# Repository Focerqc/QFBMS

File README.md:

# QFBMS — 32s charge-only BMS

QFBMS is a 32-series, charge-only battery-management board for a Fungineers pack. It uses two BQ76952 monitors and an ESP32-C3-MINI-1. The intended software is the VBMS32-target VESC Express firmware plus the supplied VBMS32 Micro package.

The board monitors cells and temperature, measures charging current, controls charging, and balances cells. **Discharge protection is outside the build scope.**

The circuit and routing are incomplete. Firmware compatibility is a design target; the current PCB has not been verified against the supplied software or validated for manufacture.

## Start here

- [Build plan](PLAN.md): the current objective, work order, open decisions, and completion criteria.
- [Design rules](DESIGN_RULES.md): mechanical constraints and how to change the working design.
- [Firmware and package interface](docs/FIRMWARE_INTERFACE.md): behavior and hardware assumptions already defined by the supplied software.

These documents supersede the proposals in [docs/history](docs/history/README.md). The historical discharge-switching instructions and blanket prohibition on moving any component are not the current build plan.

## What stays in place

Keep the placed connectors and bleed resistors R_B1–R_B33 in their existing locations for compatibility with the same case. There is no heatsink. Keep the two BMS monitors in approximately their existing areas; modest local adjustment is acceptable when needed for a sound layout.

Supporting circuitry should follow TI's applicable electrical and layout guidance while fitting these constraints. The existing C_F1–C_F32 back-side placement is a separate unresolved issue; see [Design rules](DESIGN_RULES.md).

## How the software controls the board

The package's LispBM program runs on the ESP32 inside VESC Express. It decides when charging and balancing are allowed. The board-specific C firmware supplies the hardware functions: reading the BQ monitors and commanding balancing over I2C, and controlling external charge-switch circuitry through ESP32 GPIOs.

The supplied package already implements charging voltage, temperature, and current limits, plus balancing rules. Use those definitions as the compatibility baseline. Review the physical circuit, sensing calibration, and startup wiring against them before routing. The BQ automatic-protection configuration alone does not describe the complete charging behavior.

TI supplies the electrical requirements for the monitors and their supporting circuits. A 32s design also needs the stacked-monitor communication and power-domain treatment described in [the reference notes](_reference/ti_bq76952/README.md).

## Open the design

Open `qfbms32.kicad_pro` in KiCad 10. Keep the PCB, schematic, custom footprints in `qfbms.pretty/`, footprint table, and local `3dmodels/` together.

The PCB pad nets are the current working copy. The schematic is incomplete and must be reconciled deliberately; do not overwrite the PCB with an unverified schematic netlist or an old generation script.

The saved [connectivity snapshot](docs/connectivity-snapshot.json) is a migration-era report, not a live status or electrical sign-off. Read the actual board for current connectivity. Dashboard criteria may still reflect older topology assumptions.

## Local tools

From this repository root, install the dashboard dependencies:

```powershell
python -m pip install -r requirements.txt
```

Run each dashboard in its own terminal:

```powershell
python _tools/progress_dashboard/server.py
# http://localhost:5181
```

```powershell
python _tools/pcb_dashboard/server.py
# http://localhost:5180
```

Stop older copies using those ports first. The tools currently expect KiCad 10 at `C:\Program Files\KiCad\10.0`; scripts importing `pcbnew` use KiCad's bundled Python.

## References and history

- [_reference/firmware/](_reference/firmware/): supplied VBMS32 firmware and package source, retained as the compatibility baseline.
- [_reference/ti_bq76952/](_reference/ti_bq76952/README.md): datasheet, evaluation-board material, and links to stacked-monitor guidance.
- [_reference/user_photos/](_reference/user_photos/): placement photographs; IMG_2151 shows the back.
- [Harness drawing](_reference/vfbms32_wiring_32s_best.jpg): external wiring reference; verify its connector pin mapping against the PCB.
- [_reference/pinouts/](_reference/pinouts/): preserved component pinout research.
- [docs/history/](docs/history/README.md): superseded topology, inventory, and finish instructions, retained for traceability.
- [exports/](exports/README.md): regenerated previews and reports, ignored by Git.

The original folder, experiments, and backups remain in the local source repository's migration archive. See [Migration history](docs/MIGRATION.md).

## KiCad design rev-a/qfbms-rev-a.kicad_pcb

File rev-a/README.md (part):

# QFBMS rev A

A fresh, generated attempt at the 32s charge-only BMS. It keeps the old board's outline,
connectors and R_B1–R_B33 row, and the supplied VBMS32 firmware. Everything else was redrawn
from the datasheets.

**Status (2026-11-17):** complete schematic, every part has a stated purpose, placed and
routed on 4 layers with shaped charge-path pours. **Not ready to order:** 4 connections are still
open and 7 small DRC items remain (list below), and the design assumes a conformal-coated board.
Work stopped here on purpose: rev A is a reference model, not a build commitment. Rev A is a guess-and-check
build. An outside review (below) found one critical circuit error and several major ones, so
**as drawn it would not work safely**. They are recorded, not fixed: the PCB is left as is.

| Check | Result |
|---|---|
| Parts | 193, each with a `Purpose` field (schematic property, footprint field and [bom.csv](bom.csv)) |
| Netlist vs. circuit table | 562 pins checked by kicad-cli, 0 mismatches, 0 single-pin nets |
| ERC | 0 errors, 1 expected warning (isolator GND2 sits on CELL16) |
| Fixed parts | 45 checked (connectors + R_B1–R_B33): position, rotation, side, every pad identical to `qfbms32.kicad_pcb` |
| Placement | 193/193 on the front, each inside its voltage domain (upper monitor between x 41 and 63) |
| Routing | Freerouting, 4 layers, In1 = GND / CELL16 reference planes |
| PCB DRC (coated rules) | Schematic parity 0, **4 unconnected**, 7 small errors (2 GND tracks too near the edge, 4 starved thermal reliefs, 1 dangling stub). Also 3 pin-to-pin pairs set by TI's pinouts and 6 items in the fixed parts' own footprints (see `route/drc-summary.json`) |
| PCB DRC (uncoated, 0.6 mm by voltage bank) | ~280 clearance hits: not met. Use conformal coating or re-route by hand |

## Files

| Path | What |
|---|---|
| `tools/circuit.py` | **The design.** Every part, pin→net map, value, MPN and purpose |
| `tools/gen_schematic.py` | Writes `qfbms-rev-a.kicad_sch`, `bom.csv`, the local symbol lib and lib tables |
| `tools/check_schematic.py` | kicad-cli netlist parity against `circuit.py`, plus ERC |
| `tools/build_board.py` | Writes `qfbms-rev-a.kicad_pcb` from the old board's outline and fixed parts (old file only read) and places every part by connectivity inside its voltage domain |
| `tools/set_rules.py` | Net classes (Default / POWER / HV / CHARGE) and `.kicad_dru`. `--uncoated` writes the 0.6 mm voltage-bank rules |
| `tools/route_board.py` | `export` adds the In1 planes and writes `route/*.dsn`; `import` reads Freerouting's `.ses` |
| `tools/check_board.py` | DRC + parity, sorted into real problems, chip-pinout pairs and fixed-footprint items |
| `qfbms_reva.pretty/`, `qfbms_reva.kicad_sym` | XT30, USB-C, ESP32, buzzer footprints (copied); ESP32-C3-MINI-1 and VOM1271 symbols |
| `render/` | Board render and schematic PDF |

Regenerate (KiCad 10; `KPY` = `"C:\Program Files\KiCad\10.0\bin\python.exe"`):

```
python tools/gen_schematic.py && python tools/check_schematic.py
python tools/set_rules.py
KPY tools/build_board.py
KPY tools/route_board.py export
java -jar freerouting-2.0.1.jar -de route/qfbms-rev-a.dsn -do route/qfbms-rev-a.ses -mp 100 -mt 1 -da
KPY tools/route_board.py import --no-pours
python tools/check_board.py
```

Freerouting 2.0.1 needs Java 21. Headless mode (`--gui.enabled=false`) exits without saving.
With the window it routes, saves, shows a settings pop-up and closes itself. Its settings file
(`%TEMP%\freerouting\freerouting.json`) enables telemetry by default; it was switched off here.
`route/placed-planes.kicad_pcb` is the placed, unrouted board the current route came from.

Change the design in `circuit.py` only. The schematic is label-per-pin and is never edited by hand.

## How it works

- **Monitors.** Two BQ7695202 (I2C with CRC, REG1 on at 3.3 V: what the firmware expects).
  U_BQ1 does cells 1–16 against GND. U_BQ2 does cells 17–32 against CELL16. Each has TI's
  typical supply: a BAT diode with RC, a BCX56-16 (80 V, SOT-89) REG0 preregulator with its own collector
  diode, a 10 MΩ BREG resistor, 22 nF on REGIN, 2.2 µF on REG18, 1 µF on REG1, and 2.2 µF from CP1 to BAT.
- **Cell inputs.** R_B1–R_B33 (27 Ω, fixed row) are the cell input resistors, one per tap.
  Tap 16 is shared by both monitors. 32 × 100 nF differential capacitors. Internal balancing ≈ 50 mA.
- **Always awake.** A 10 kΩ from TS2 to VSS wakes each monitor from SHUTDOWN (TI's note on
  thermistors at TS2). The firmware only uses DEEPSLEEP, so no wake circuit is needed.
  PACK has 10 kΩ to its own top of stack and LD goes to VSS (TI: no high-side FETs).
- **Current.** One 1 mΩ shunt between BAT− and charger negative, Kelvin-tied with net ties,
  100 Ω/100 nF filter. The Micro package scales the firmware's 0.2 mΩ gain by −0.2, so 1 mΩ
  with SRP on the battery side is what it expects (PCB_VERSION 2). No firmware change needed.
- **Temperatures.** J_T1–J_T4 go to TS1, TS3, ALERT and DCHG. RT1, beside the FETs, goes to HDQ.
  Each has a 499 Ω series resistor (the firmware subtracts 500 Ω), with a 10 k B3380 NTC.
- **Charge switch.** Q1 and Q2 are back-to-back 200 V N-FETs (TOLL), so the charge port is dead
  either way when off. A VOM1271 photovoltaic driver makes the floating ~8 V gate drive with
  no high-side supply. Its LED needs both CHG_EN (GPIO5) **and** PSW_EN (GPIO10), matching the
  firmware's order.
- **Upper-monitor link.** The host I2C bus goes through two 74CBTLV1G125 bus switches to an
  ISO1640. COM_EN (GPIO9) high opens the switches, so the firmware can re-address U_BQ1
  while U_BQ2 is hidden. The isolator's upper side runs from U_BQ2's REG1 through a PFET.
  An opto turns that PFET on only while COM_EN is low, so the isolator doesn't drain cells
  17–32 in sleep.
- **Power.** LTC7138 (140 V) from the fused pack through a 100 Ω/2 µF filter, to 5.0 V. It is
  diode-ORed with USB VBUS, then an AP2112K makes 3.3 V. The ESP32 can be flashed over USB
  without the pack.
- **ESP32-C3-MINI-1.** Pins exactly as `hw_vbms32.h`. GPIO2 (ENABLE) idles low with a wake
  button to 3.3 V, because the firmware treats high as "stay awake". GPIO8/GPIO9 straps are
  pulled high. 2.2 MΩ/47 kΩ dividers keep the firmware's 220k/4.7k ratio at 1/10 the drain.
- **CAN.** ISO1050 isolated, side 2 powered from the VESC's 5 V on J_COMM1, with an optional
  120 Ω termination behind solder jumper JP1.

## Removed from the old board, and why

| Old parts | Why they are gone |
|---|---|
| R_F1–R_F32 (20 Ω) | Second series row. R_B1–R_B33 already are the cell input resistors |
| R_SH2 | Second shunt. One 1 mΩ matches the firmware scaling |
| U_SSR1 "GSRELAY", C_SSR1/2, R_SSR1/2 | Unidentified relay/driver. Replaced by the VOM1271 |
| D_BST1, D_PRI1–3, D_SEC1–3, R_SEC1, FB1, C_TAN1, C_FLT1, C_DISC | Old boost/isolated-supply gate-drive attempt. The photovoltaic driver needs none of it |
| D_CHG1–3 (DSK320), R_CHG1/2, R_DSG1, R_S1/2, R_G1, R_GS1, D_GS1, D_S1 | Old charge/discharge-path parts. Discharge is out of scope; the new charge path is Q1/Q2, R1, D1 |
| EP pad on U_BQ1/U_BQ2 footprints | The BQ76952 TQFP-48 has no exposed pad |

U4 (LTC7138), U7 (ISO1050), Q1, F1, BZ1, the C_F caps and U_BQ1/U_BQ2 keep their references
with new circuits.

## External review (2026-11-17, recorded, not fixed)

A ChatGPT review of `circuit.py`, the README, the BOM, the firmware and the PCB. Its local
copies were used; it could not open the public links. The top finding was checked against
`circuit.py` and is correct. Decision: leave the PCB as is and record everything here.

### Hardware (rev A design errors)

| Severity | Part / net | Finding | Fix if rev B happens |
|---|---|---|---|
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
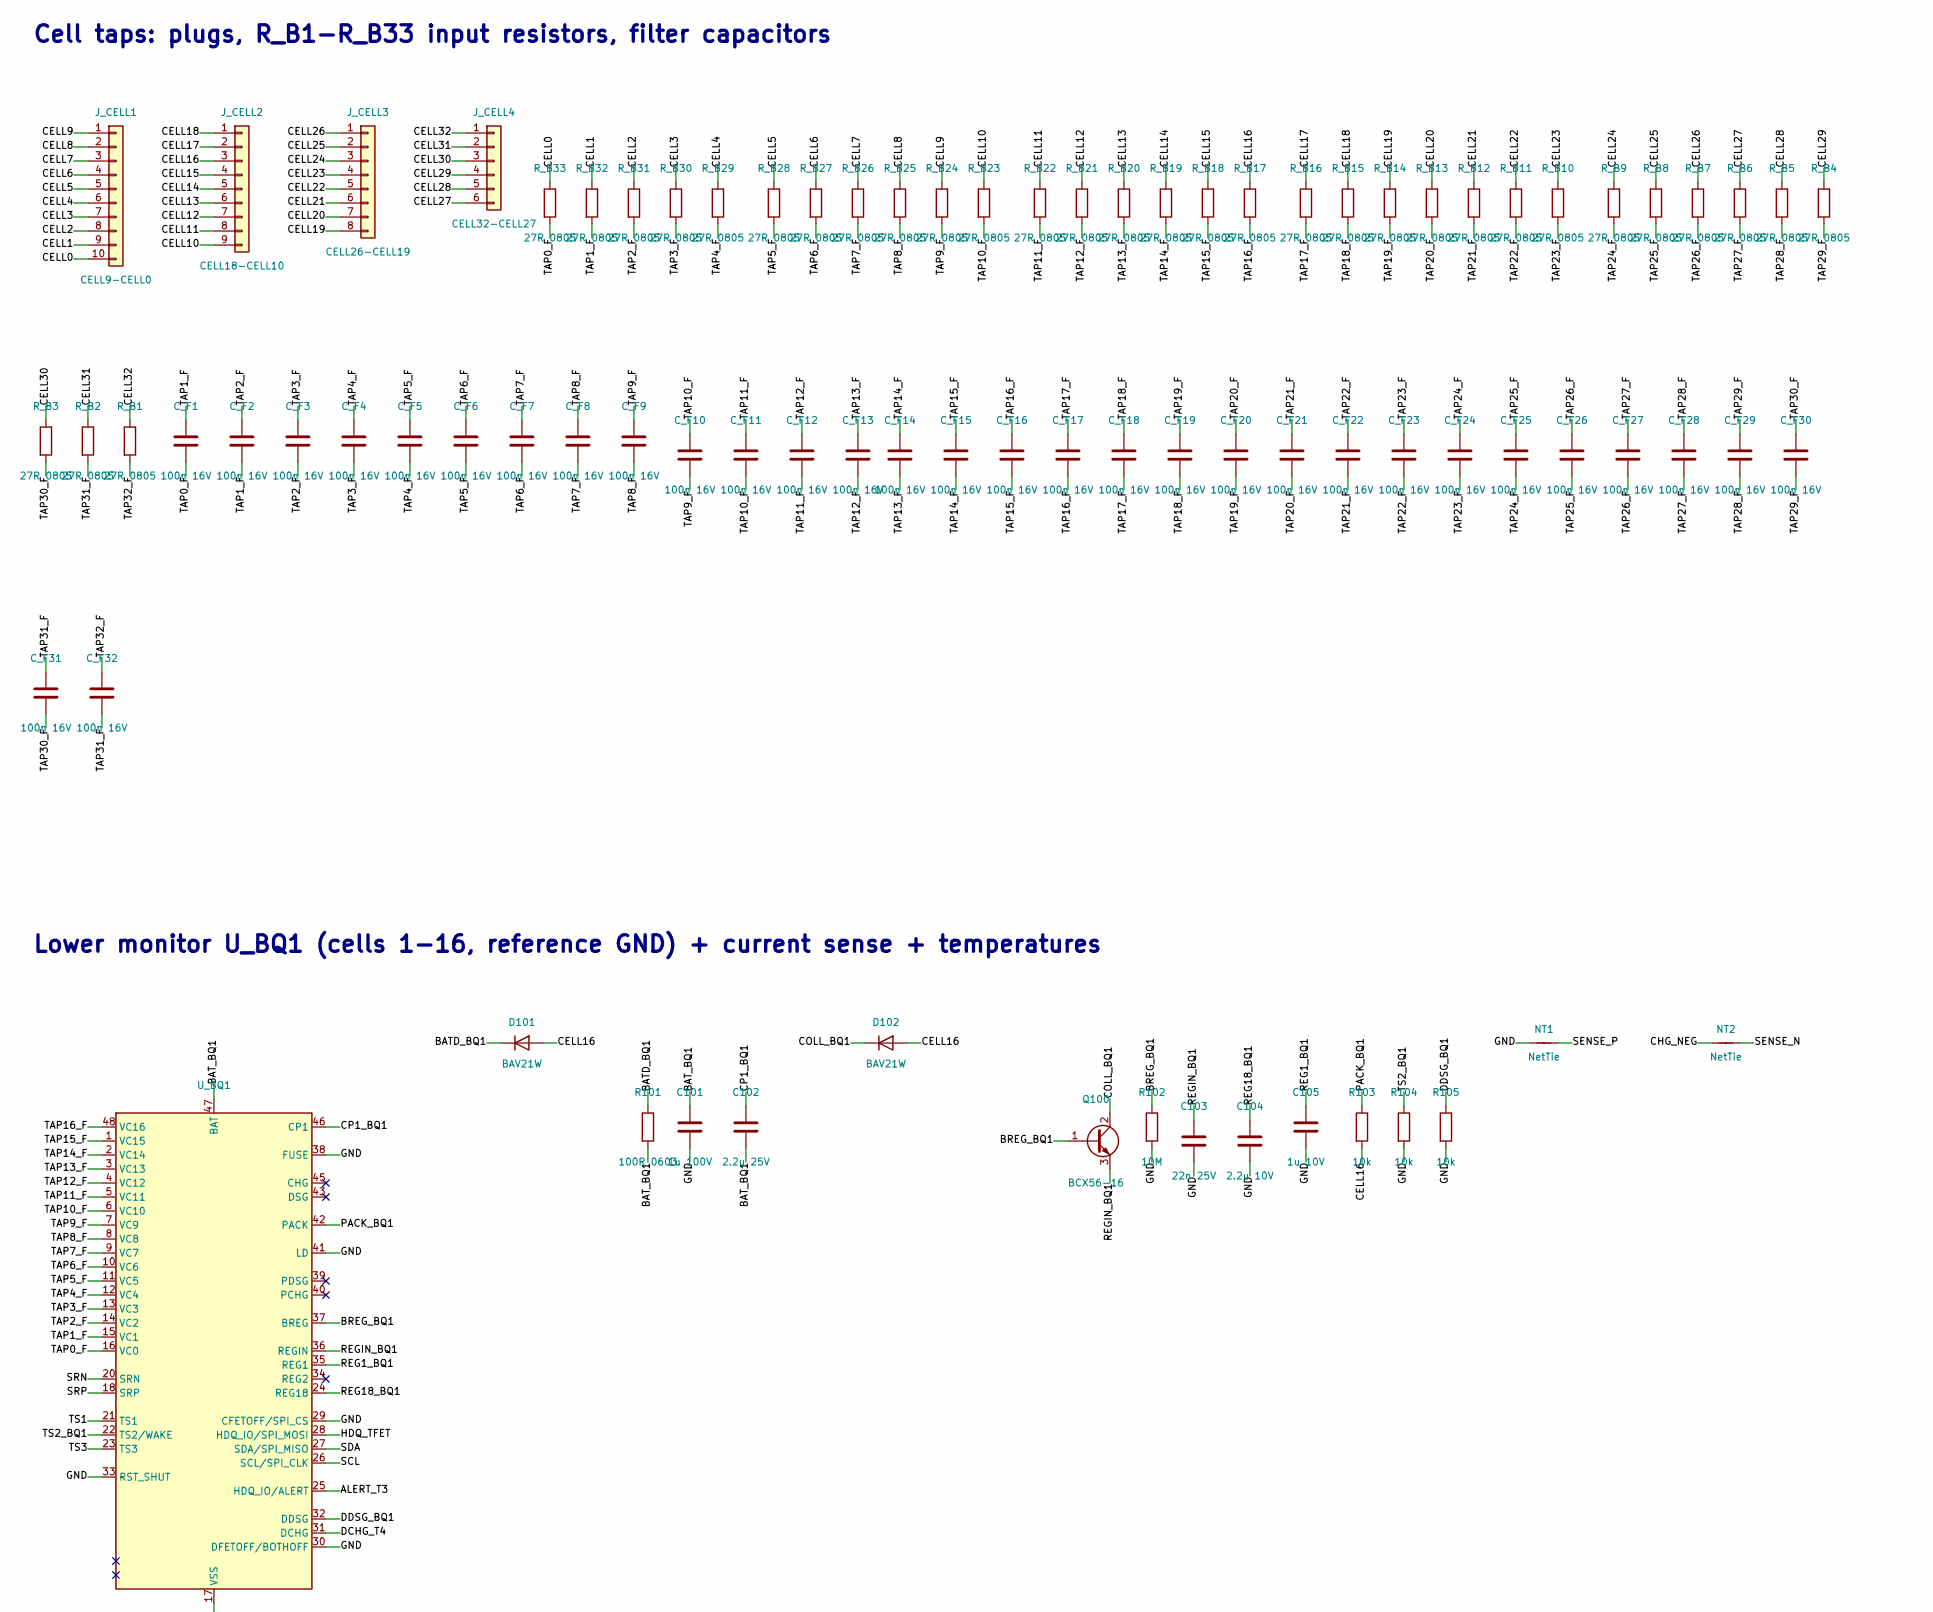
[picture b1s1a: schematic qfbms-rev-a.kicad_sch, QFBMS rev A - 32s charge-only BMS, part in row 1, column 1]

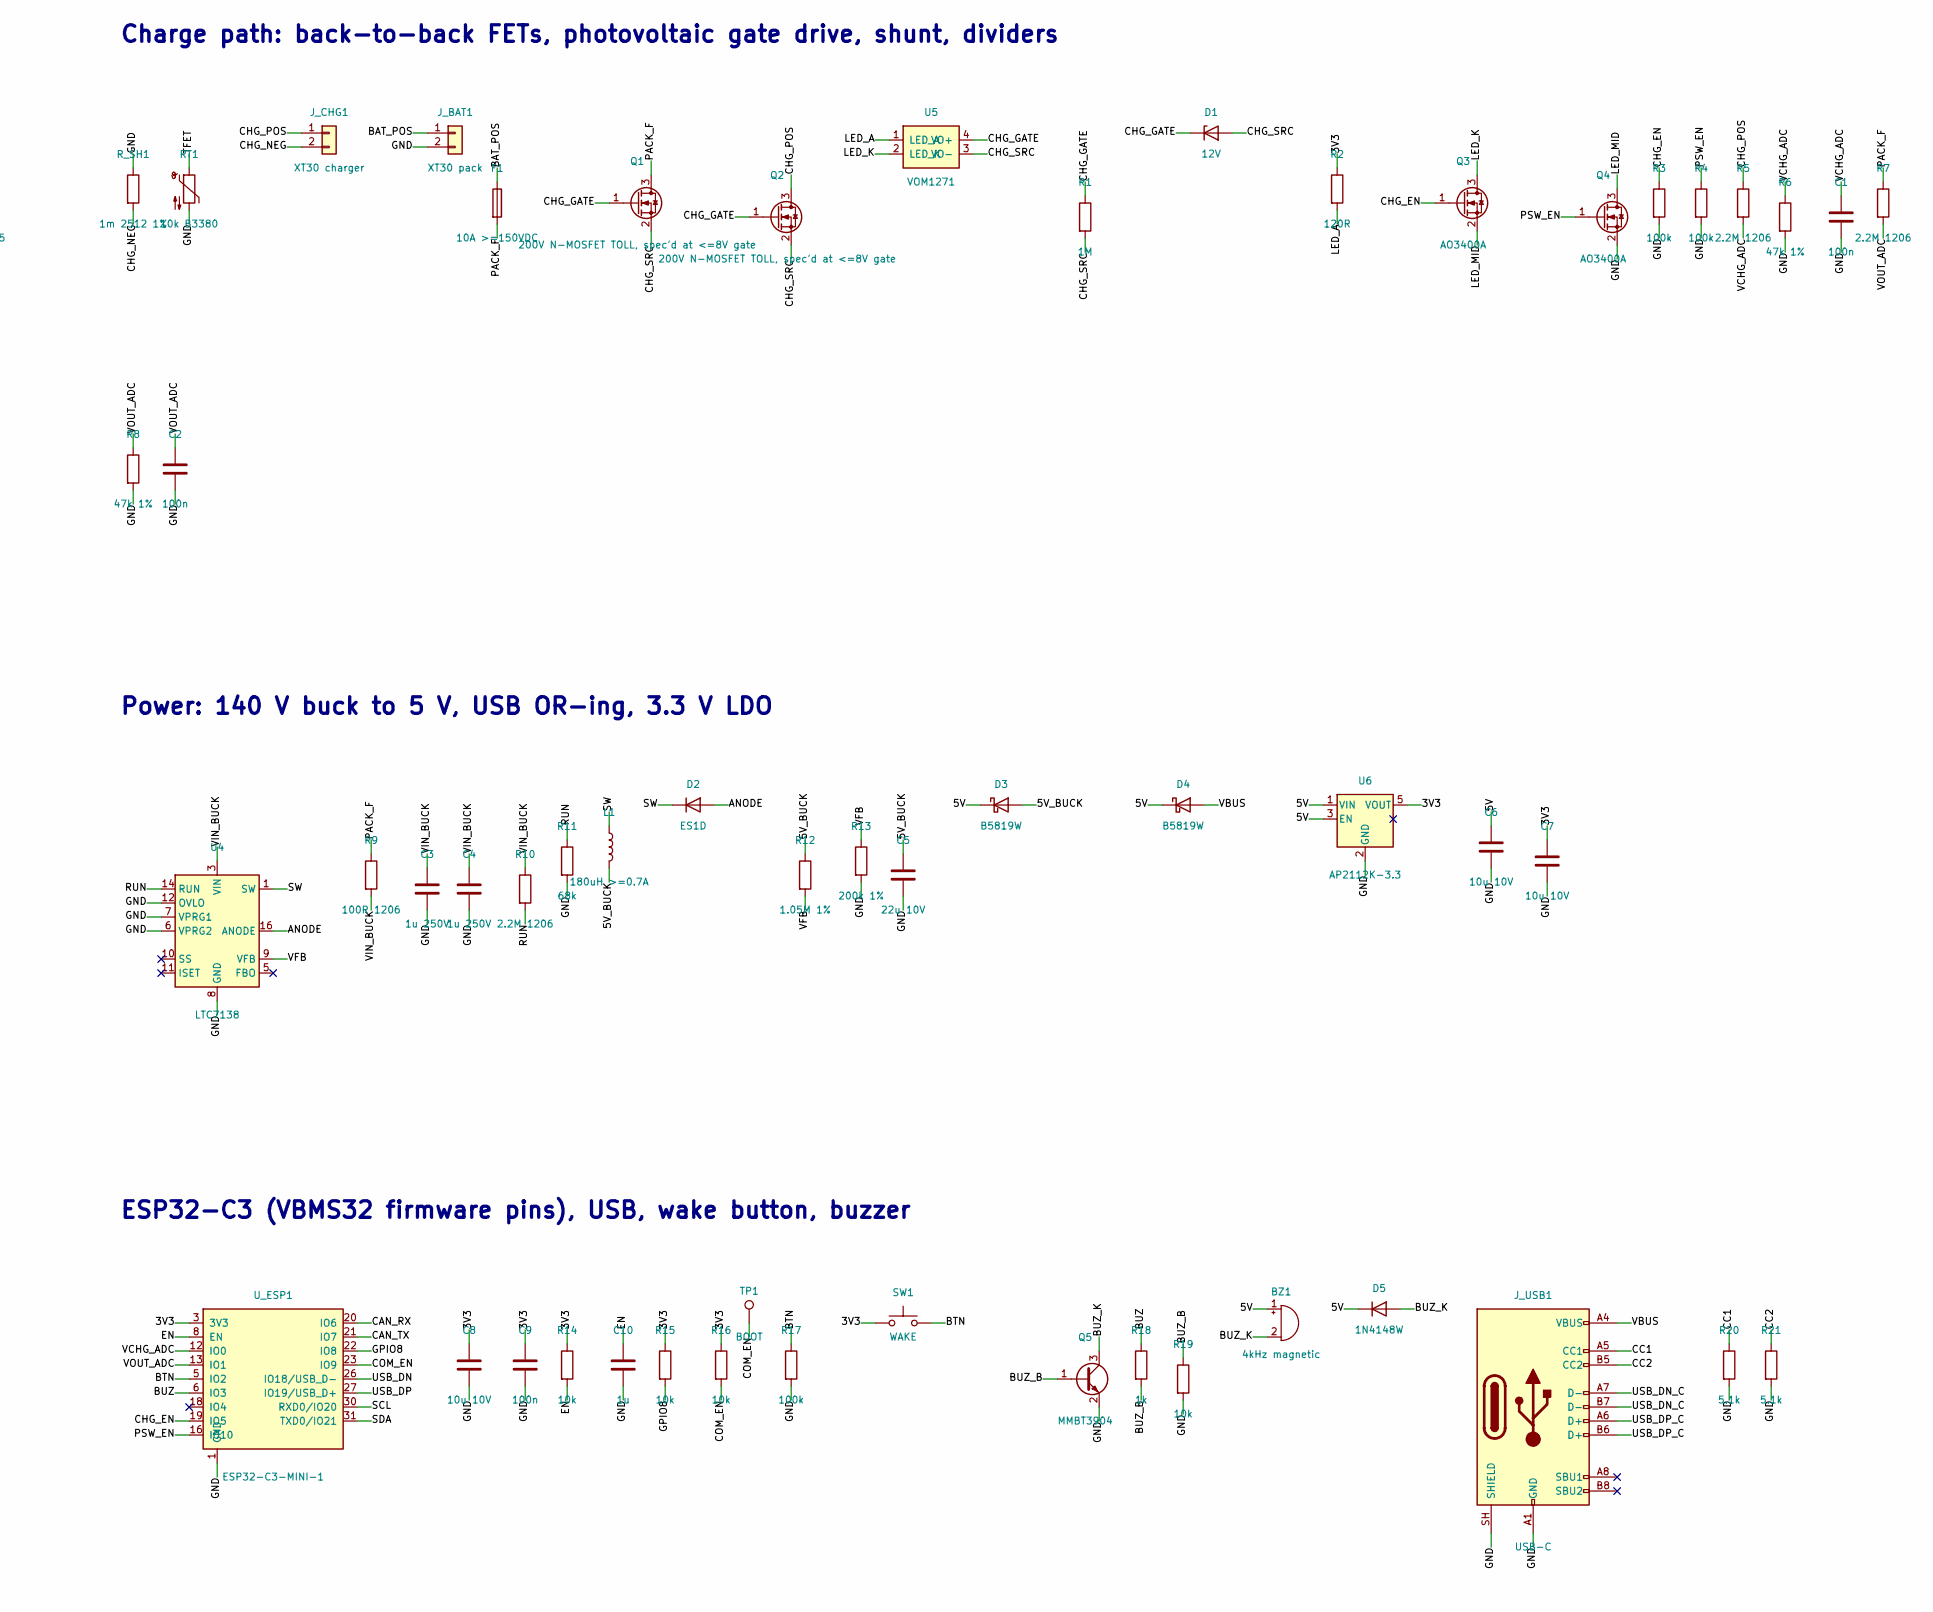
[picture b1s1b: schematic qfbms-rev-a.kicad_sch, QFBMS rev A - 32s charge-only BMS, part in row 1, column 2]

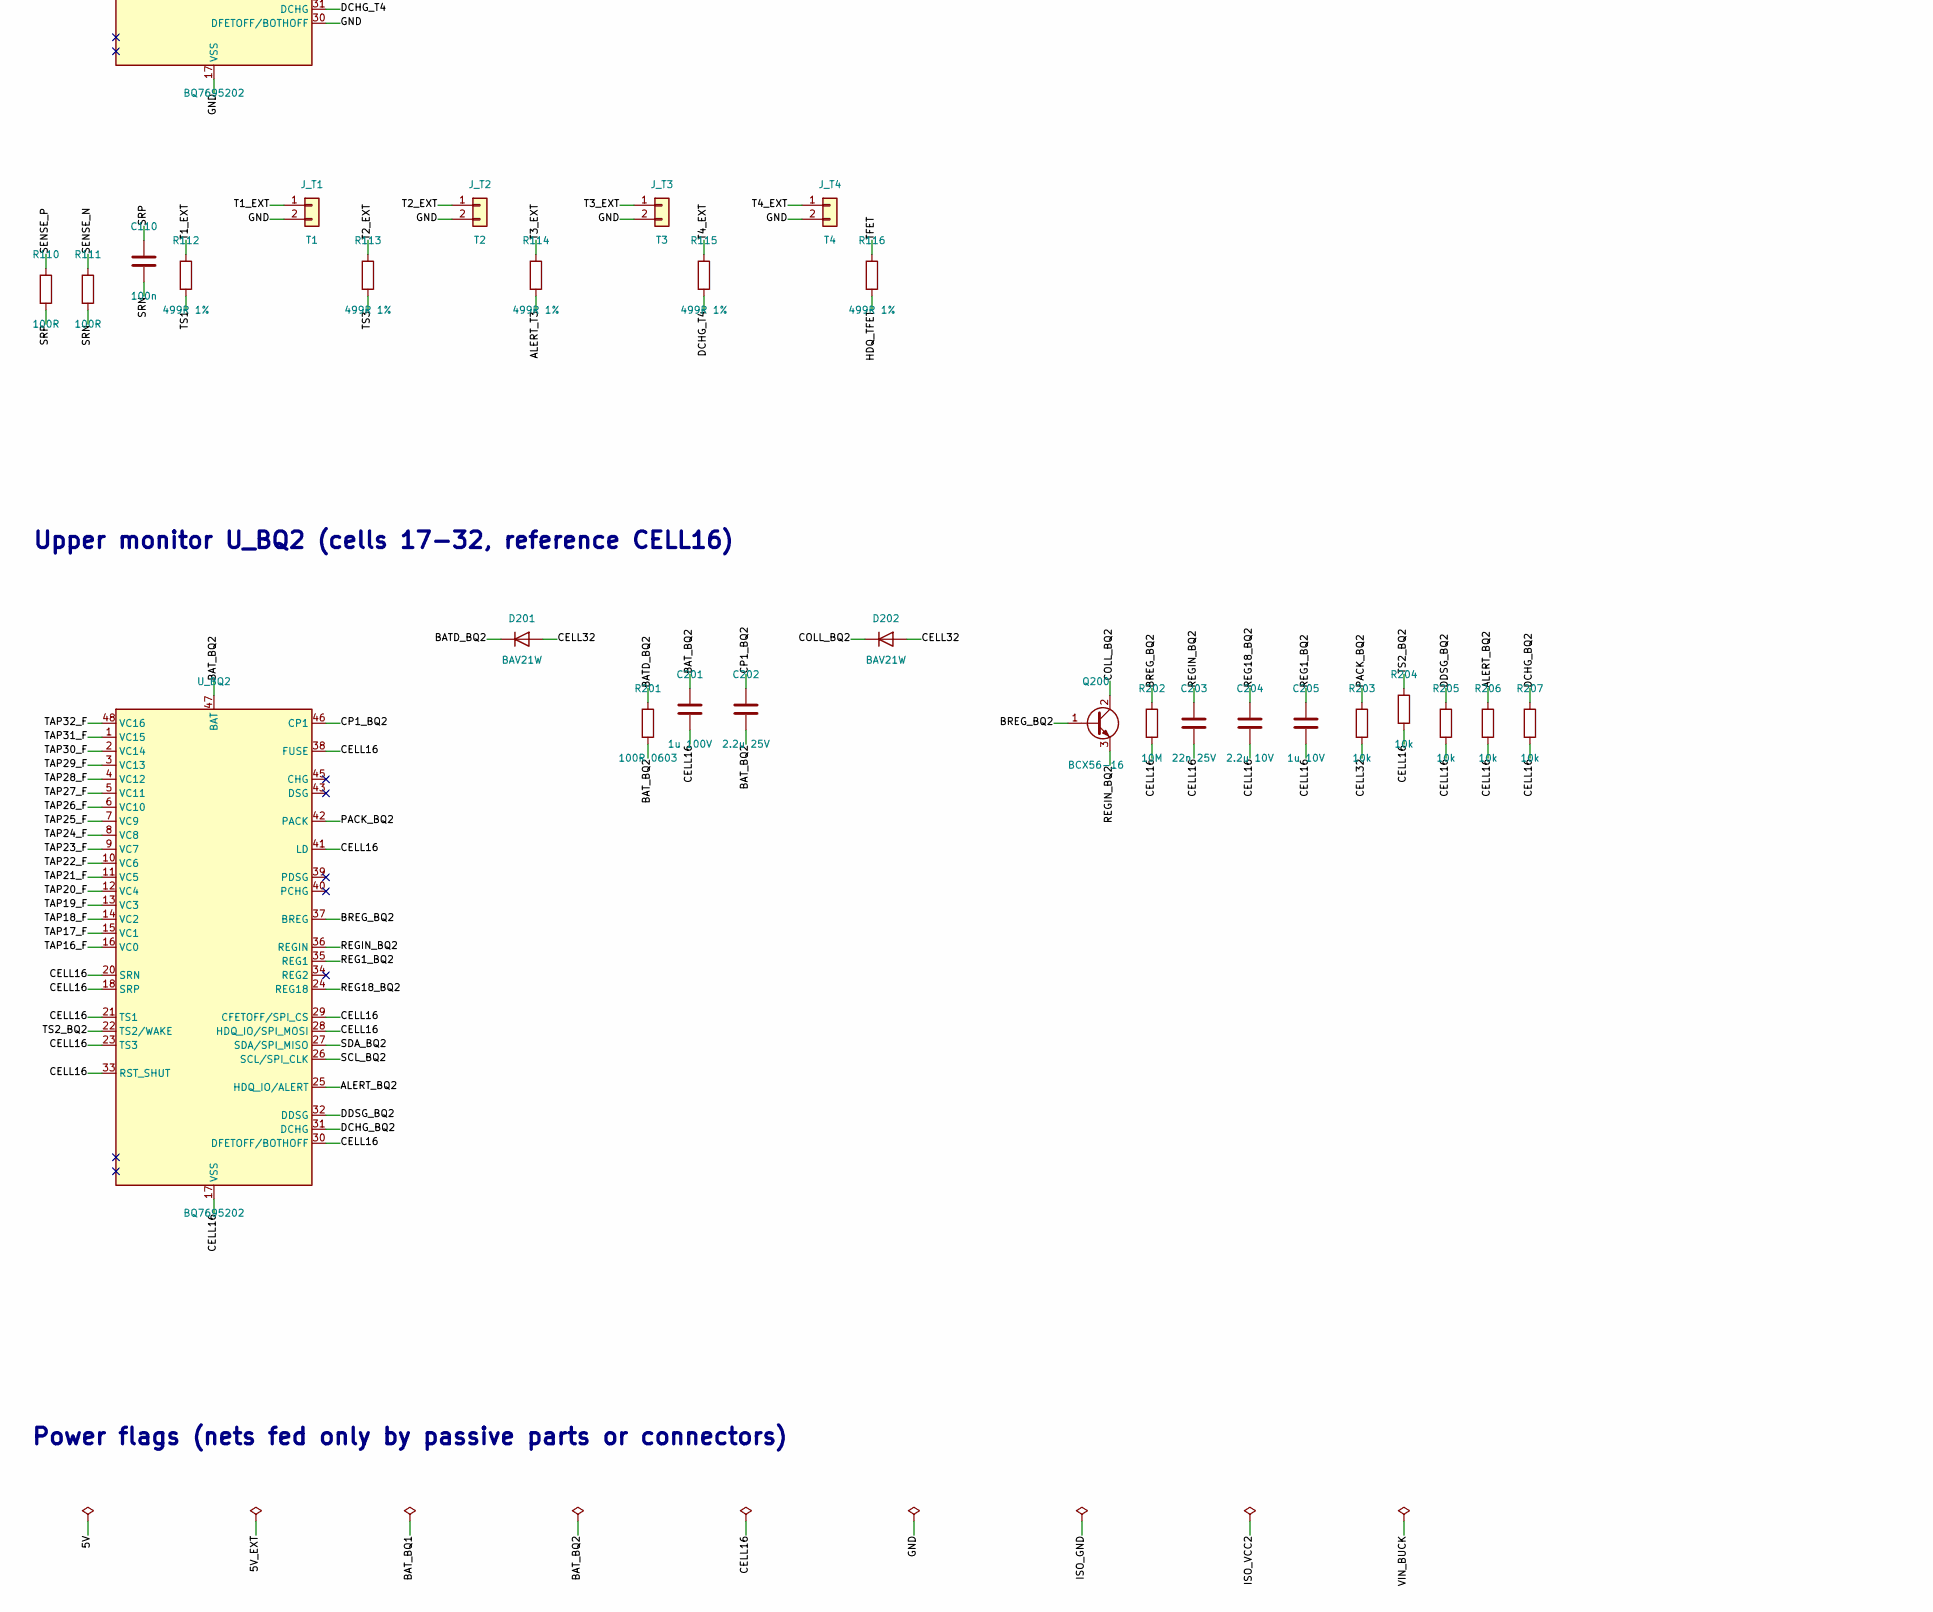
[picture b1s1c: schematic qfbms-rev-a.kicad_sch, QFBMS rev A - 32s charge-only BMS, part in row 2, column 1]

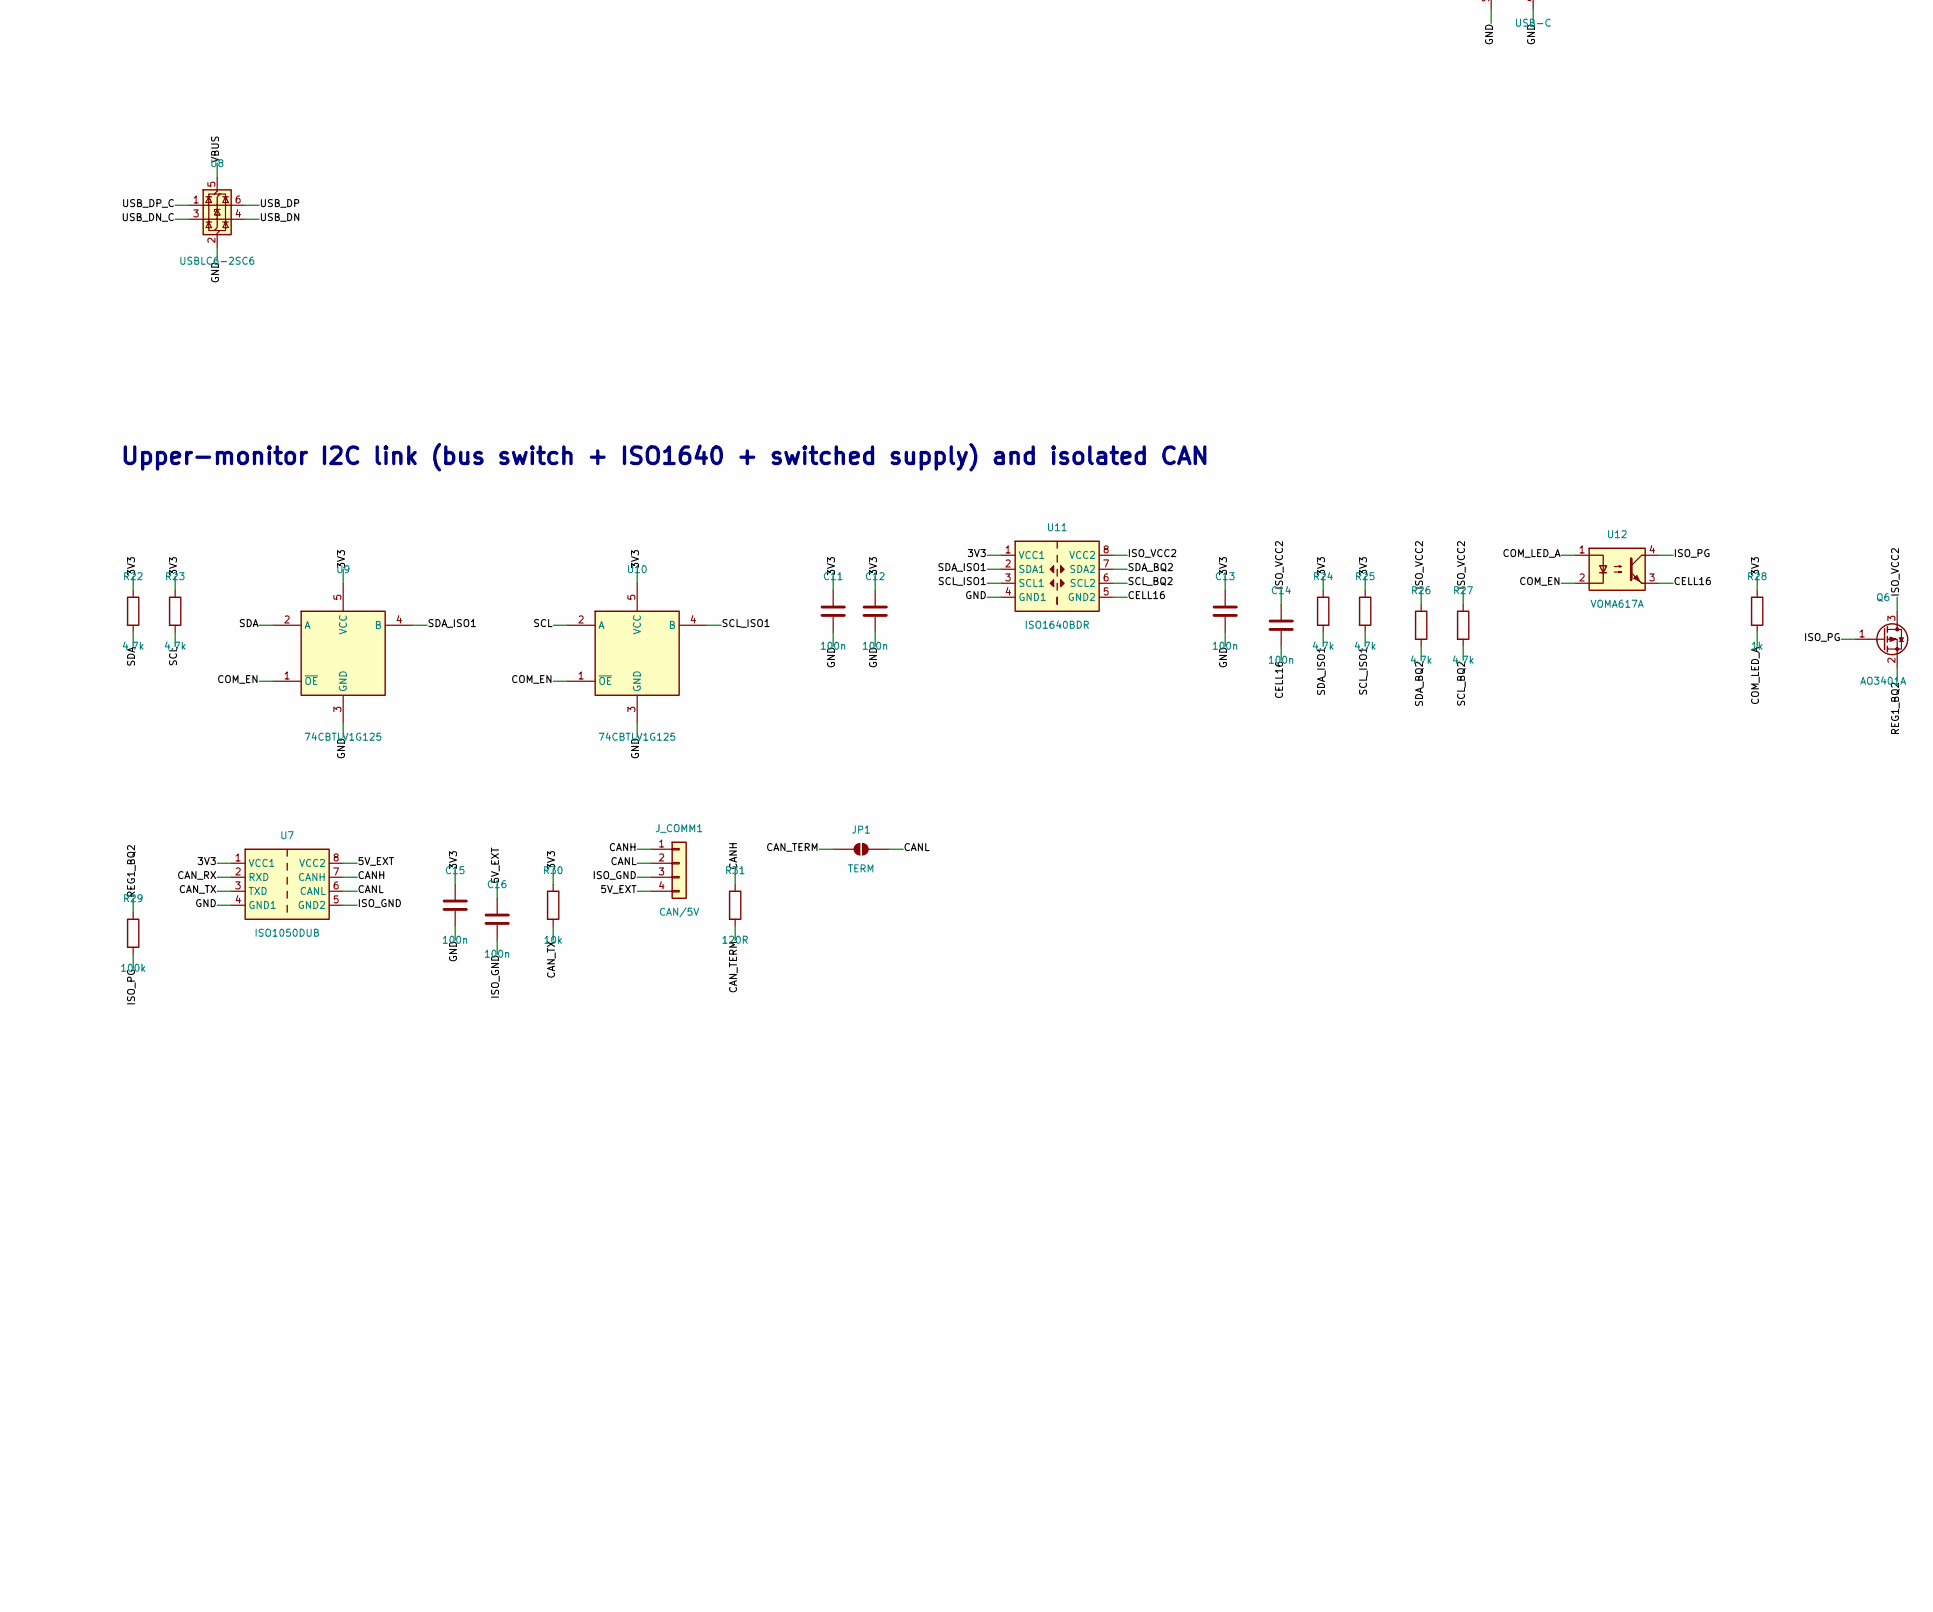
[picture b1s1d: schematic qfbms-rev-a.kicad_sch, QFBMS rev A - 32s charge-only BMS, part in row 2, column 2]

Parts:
BZ1: 4kHz magnetic; Buzzer_5.0x5.0mm_SMD; MPN 5x5 mm magnetic transducer, 4 kHz, 5 V
C1, C2, C9, C11, C12, C13, C14, C15, C16, C110: 100n; C_0402_1005Metric
C3, C4: 1u 250V; C_1210_3225Metric
C5: 22u 10V; C_1206_3216Metric
C6, C7, C8: 10u 10V; C_0805_2012Metric
C10: 1u; C_0603_1608Metric
C101, C201: 1u 100V; C_0805_2012Metric
C102, C202: 2.2u 25V; C_0603_1608Metric
C103, C203: 22n 25V; C_0402_1005Metric
C104, C204: 2.2u 10V; C_0603_1608Metric
C105, C205: 1u 10V; C_0603_1608Metric
C_F1, C_F2, C_F3, C_F4, C_F5, C_F6, C_F7, C_F8, C_F9, C_F10, C_F11, C_F12, C_F13, C_F14, C_F15, C_F16, C_F17, C_F18, C_F19, C_F20, C_F21, C_F22, C_F23, C_F24, C_F25, C_F26, C_F27, C_F28, C_F29, C_F30, C_F31, C_F32: 100n 16V; C_0402_1005Metric
D1: 12V; D_SOD-123; MPN BZT52C12
D2: ES1D; D_SMA; MPN ES1D
D3, D4: B5819W; D_SOD-123; MPN B5819W
D5: 1N4148W; D_SOD-123; MPN 1N4148W
D101, D102, D201, D202: BAV21W; D_SOD-123; MPN BAV21W
F1: 10A >=150VDC; Fuse_2920_7451Metric; MPN OPEN
JP1: TERM; SolderJumper-2_P1.3mm_Open_RoundedPad1.0x1.5mm
J_BAT1: XT30 pack; XT30PW-M_Lugs
J_CELL1: CELL9-CELL0; JST_GH_BM10B-GHS-TBT_1x10-1MP_P1.25mm_Vertical
J_CELL2: CELL18-CELL10; JST_GH_BM09B-GHS-TBT_1x09-1MP_P1.25mm_Vertical
J_CELL3: CELL26-CELL19; JST_GH_BM08B-GHS-TBT_1x08-1MP_P1.25mm_Vertical
J_CELL4: CELL32-CELL27; JST_GH_BM06B-GHS-TBT_1x06-1MP_P1.25mm_Vertical
J_CHG1: XT30 charger; XT30PW-F_Lugs
J_COMM1: CAN/5V; JST_GH_BM04B-GHS-TBT_1x04-1MP_P1.25mm_Vertical
J_T1: T1; JST_GH_BM02B-GHS-TBT_1x02-1MP_P1.25mm_Vertical
J_T2: T2; JST_GH_BM02B-GHS-TBT_1x02-1MP_P1.25mm_Vertical
J_T3: T3; JST_GH_BM02B-GHS-TBT_1x02-1MP_P1.25mm_Vertical
J_T4: T4; JST_GH_BM02B-GHS-TBT_1x02-1MP_P1.25mm_Vertical
J_USB1: USB-C; USB_C_Receptacle_16P
L1: 180uH >=0.7A; L_7.3x7.3_H4.5; MPN 180 uH shielded 7.3x7.3, Isat >= 0.7 A
NT1, NT2: NetTie; NetTie-2_SMD_Pad0.5mm
Q1, Q2: 200V N-MOSFET TOLL, spec'd at <=8V gate; Infineon_PG-HSOF-8-1; MPN e.g. IPT111N20NFD (confirm)
Q3, Q4: AO3400A; SOT-23; MPN AO3400A
Q5: MMBT3904; SOT-23; MPN MMBT3904
Q6: AO3401A; SOT-23; MPN AO3401A
Q100, Q200: BCX56-16; SOT-89-3; MPN BCX56-16
R1: 1M; R_0402_1005Metric
R2, R31: 120R; R_0402_1005Metric
R3, R4, R17, R29: 100k; R_0402_1005Metric
R5, R7, R10: 2.2M 1206; R_1206_3216Metric
R6, R8: 47k 1%; R_0402_1005Metric
R9: 100R 1206; R_1206_3216Metric
R11: 68k; R_0402_1005Metric
R12: 1.05M 1%; R_0402_1005Metric
R13: 200k 1%; R_0402_1005Metric
R14, R15, R16, R19, R30, R103, R104, R105, R203, R204, R205, R206, R207: 10k; R_0402_1005Metric
R18, R28: 1k; R_0402_1005Metric
R20, R21: 5.1k; R_0402_1005Metric
R22, R23, R24, R25, R26, R27: 4.7k; R_0402_1005Metric
R101, R201: 100R 0603; R_0603_1608Metric
R102, R202: 10M; R_0402_1005Metric
R110, R111: 100R; R_0402_1005Metric
R112, R113, R114, R115, R116: 499R 1%; R_0402_1005Metric
RT1: 10k B3380; R_0603_1608Metric; MPN NCP18XH103F03RB
R_B1, R_B2, R_B3, R_B4, R_B5, R_B6, R_B7, R_B8, R_B9, R_B10, R_B11, R_B12, R_B13, R_B14, R_B15, R_B16, R_B17, R_B18, R_B19, R_B20, R_B21, R_B22, R_B23, R_B24, R_B25, R_B26, R_B27, R_B28, R_B29, R_B30, R_B31, R_B32, R_B33: 27R 0805; R_0805_2012Metric
R_SH1: 1m 2512 1%; R_2512_6332Metric; MPN 1 mOhm 2512 metal strip, TCR <= 50 ppm
SW1: WAKE; SW_SPST_PTS810
TP1: BOOT; TestPoint_Pad_D1.0mm
U4: LTC7138; Analog_MSOP-12-16-1EP_3x4.039mm_P0.5mm_EP1.651x2.845mm; MPN LTC7138EMSE#PBF
U5: VOM1271; SOP-4_4.4x2.6mm_P1.27mm; MPN VOM1271T
U6: AP2112K-3.3; SOT-23-5; MPN AP2112K-3.3TRG1
U7: ISO1050DUB; SOP-8_6.62x9.15mm_P2.54mm; MPN ISO1050DUBR
U8: USBLC6-2SC6; SOT-23-6; MPN USBLC6-2SC6
U9, U10: 74CBTLV1G125; SOT-353_SC-70-5; MPN SN74CBTLV1G125DCKR
U11: ISO1640BDR; SOIC-8_3.9x4.9mm_P1.27mm; MPN ISO1640BDR
U12: VOMA617A; SOP-4_4.4x2.6mm_P1.27mm; MPN VOMA617A-3X001T
U_BQ1, U_BQ2: BQ7695202; TQFP-48_7x7mm_P0.5mm; MPN BQ7695202PFBR
U_ESP1: ESP32-C3-MINI-1; MPN ESP32-C3-MINI-1-N4

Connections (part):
/3V3: C7.1, C8.1, C9.1, C11.1, C12.1, C13.1, C15.1, R2.1, R14.1, R15.1, R16.1, R22.1, R23.1, R24.1, R25.1, R28.1, R30.1, SW1.1, U6.5 (VOUT), U7.1 (VCC1), U9.5 (VCC), U10.5 (VCC), U11.1 (VCC1), U_ESP1.3 (3V3)
/5V: BZ1.1 (+), C6.1, D3.1 (K), D4.1 (K), D5.1 (K), U6.1 (VIN), U6.3 (EN)
/5V_BUCK: C5.1, D3.2 (A), L1.2, R12.1
/5V_EXT: C16.1, J_COMM1.4, U7.8 (VCC2)
/ALERT_BQ2: R206.1, U_BQ2.25 (HDQ_IO/ALERT)
/ALERT_T3: R114.2, U_BQ1.25 (HDQ_IO/ALERT)
/ANODE: D2.2 (A), U4.16 (ANODE)
/BATD_BQ1: D101.1 (K), R101.1
/BATD_BQ2: D201.1 (K), R201.1
/BAT_BQ1: C101.1, C102.2, R101.2, U_BQ1.47 (BAT)
/BAT_BQ2: C201.1, C202.2, R201.2, U_BQ2.47 (BAT)
/BAT_POS: F1.1, J_BAT1.1
/BREG_BQ1: Q100.1 (B), R102.1, U_BQ1.37 (BREG)
/BREG_BQ2: Q200.1 (B), R202.1, U_BQ2.37 (BREG)
/BTN: R17.1, SW1.2, U_ESP1.5 (IO2)
/BUZ: R18.1, U_ESP1.6 (IO3)
/BUZ_B: Q5.1 (B), R18.2, R19.1
/BUZ_K: BZ1.2 (-), D5.2 (A), Q5.3 (C)
/CANH: J_COMM1.1, R31.1, U7.7 (CANH)
/CANL: JP1.2 (B), J_COMM1.2, U7.6 (CANL)
/CAN_RX: U7.2 (RXD), U_ESP1.20 (IO6)
/CAN_TERM: JP1.1 (A), R31.2
/CAN_TX: R30.2, U7.3 (TXD), U_ESP1.21 (IO7)
/CC1: J_USB1.A5 (CC1), R20.1
/CC2: J_USB1.B5 (CC2), R21.1
/CELL0: J_CELL1.10, R_B33.1
/CELL1: J_CELL1.9, R_B32.1
/CELL2: J_CELL1.8, R_B31.1
/CELL3: J_CELL1.7, R_B30.1
/CELL4: J_CELL1.6, R_B29.1
/CELL5: J_CELL1.5, R_B28.1
/CELL6: J_CELL1.4, R_B27.1
/CELL7: J_CELL1.3, R_B26.1
/CELL8: J_CELL1.2, R_B25.1
/CELL9: J_CELL1.1, R_B24.1
/CELL10: J_CELL2.9, R_B23.1
/CELL11: J_CELL2.8, R_B22.1
/CELL12: J_CELL2.7, R_B21.1
/CELL13: J_CELL2.6, R_B20.1
/CELL14: J_CELL2.5, R_B19.1
/CELL15: J_CELL2.4, R_B18.1
/CELL16: C14.2, C201.2, C203.2, C204.2, C205.2, D101.2 (A), D102.2 (A), J_CELL2.3, R103.2, R202.2, R204.2, R205.2, R206.2, R207.2, R_B17.1, U11.5 (GND2), U12.3, U_BQ2.17 (VSS), U_BQ2.18 (SRP), U_BQ2.20 (SRN), U_BQ2.21 (TS1), U_BQ2.23 (TS3), U_BQ2.28 (HDQ_IO/SPI_MOSI), U_BQ2.29 (CFETOFF/SPI_CS), U_BQ2.30 (DFETOFF/BOTHOFF), U_BQ2.33 (RST_SHUT), U_BQ2.38 (FUSE), U_BQ2.41 (LD)
/CELL17: J_CELL2.2, R_B16.1
/CELL18: J_CELL2.1, R_B15.1
/CELL19: J_CELL3.8, R_B14.1
/CELL20: J_CELL3.7, R_B13.1
/CELL21: J_CELL3.6, R_B12.1
/CELL22: J_CELL3.5, R_B11.1
/CELL23: J_CELL3.4, R_B10.1
/CELL24: J_CELL3.3, R_B9.1
/CELL25: J_CELL3.2, R_B8.1
/CELL26: J_CELL3.1, R_B7.1
/CELL27: J_CELL4.6, R_B6.1
/CELL28: J_CELL4.5, R_B5.1
/CELL29: J_CELL4.4, R_B4.1
/CELL30: J_CELL4.3, R_B3.1
/CELL31: J_CELL4.2, R_B2.1
/CELL32: D201.2 (A), D202.2 (A), J_CELL4.1, R203.2, R_B1.1
/CHG_EN: Q3.1 (G), R3.1, U_ESP1.19 (IO5)
/CHG_GATE: D1.1 (K), Q1.1 (G), Q2.1 (G), R1.1, U5.4 (VO+)
/CHG_NEG: J_CHG1.2, NT2.1, R_SH1.2
/CHG_POS: J_CHG1.1, Q2.3 (D), R5.1
/CHG_SRC: D1.2 (A), Q1.2 (S), Q2.2 (S), R1.2, U5.3 (VO-)
/COLL_BQ1: D102.1 (K), Q100.2 (C)
/COLL_BQ2: D202.1 (K), Q200.2 (C)
/COM_EN: R16.2, TP1.1, U9.1 (~OE), U10.1 (~OE), U12.2, U_ESP1.23 (IO9)
/COM_LED_A: R28.2, U12.1
/CP1_BQ1: C102.1, U_BQ1.46 (CP1)
/CP1_BQ2: C202.1, U_BQ2.46 (CP1)
/DCHG_BQ2: R207.1, U_BQ2.31 (DCHG)
/DCHG_T4: R115.2, U_BQ1.31 (DCHG)
/DDSG_BQ1: R105.1, U_BQ1.32 (DDSG)
/DDSG_BQ2: R205.1, U_BQ2.32 (DDSG)
/EN: C10.1, R14.2, U_ESP1.8 (EN)
/GND: C1.2, C2.2, C3.2, C4.2, C5.2, C6.2, C7.2, C8.2, C9.2, C10.2, C11.2, C12.2, C13.2, C15.2, C101.2, C103.2, C104.2, C105.2, J_BAT1.2, J_T1.2, J_T2.2, J_T3.2, J_T4.2, J_USB1.A1 (GND), J_USB1.A12 (GND), J_USB1.B1 (GND), J_USB1.B12 (GND), J_USB1.SH (SHIELD), NT1.1, Q4.2 (S), Q5.2 (E), R3.2, R4.2, R6.2, R8.2, R11.2, R13.2, R17.2, R19.2, R20.2, R21.2, R102.2, R104.2, R105.2, RT1.2, R_SH1.1, U4.6 (VPRG2), U4.7 (VPRG1), U4.8 (GND), U4.12 (OVLO), U4.17 (GND), U6.2 (GND), U7.4 (GND1), U8.2 (GND), U9.3 (GND), U10.3 (GND), U11.4 (GND1), U_BQ1.17 (VSS), U_BQ1.29 (CFETOFF/SPI_CS), U_BQ1.30 (DFETOFF/BOTHOFF), U_BQ1.33 (RST_SHUT), U_BQ1.38 (FUSE), U_BQ1.41 (LD), U_ESP1.1 (GND), U_ESP1.2 (GND), U_ESP1.11 (GND), U_ESP1.14 (GND), U_ESP1.36 (GND), U_ESP1.37 (GND), U_ESP1.38 (GND), U_ESP1.39 (GND), U_ESP1.40 (GND), U_ESP1.41 (GND), U_ESP1.42 (GND), U_ESP1.43 (GND), U_ESP1.44 (GND), U_ESP1.45 (GND), U_ESP1.46 (GND), U_ESP1.47 (GND), U_ESP1.48 (GND), U_ESP1.49 (GND)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
/GPIO8: R15.2, U_ESP1.22 (IO8)
/HDQ_TFET: R116.2, U_BQ1.28 (HDQ_IO/SPI_MOSI)
/ISO_GND: C16.2, J_COMM1.3, U7.5 (GND2)
/ISO_PG: Q6.1 (G), R29.2, U12.4
/ISO_VCC2: C14.1, Q6.3 (D), R26.1, R27.1, U11.8 (VCC2)
/LED_A: R2.2, U5.1 (LED_A)
/LED_K: Q3.3 (D), U5.2 (LED_K)
/LED_MID: Q3.2 (S), Q4.3 (D)
/PACK_BQ1: R103.1, U_BQ1.42 (PACK)
/PACK_BQ2: R203.1, U_BQ2.42 (PACK)
/PACK_F: F1.2, Q1.3 (D), R7.1, R9.1
/PSW_EN: Q4.1 (G), R4.1, U_ESP1.16 (IO10)
/REG1_BQ1: C105.1, U_BQ1.35 (REG1)
/REG1_BQ2: C205.1, Q6.2 (S), R29.1, U_BQ2.35 (REG1)
/REG18_BQ1: C104.1, U_BQ1.24 (REG18)
/REG18_BQ2: C204.1, U_BQ2.24 (REG18)
/REGIN_BQ1: C103.1, Q100.3 (E), U_BQ1.36 (REGIN)
/REGIN_BQ2: C203.1, Q200.3 (E), U_BQ2.36 (REGIN)
/RUN: R10.2, R11.1, U4.14 (RUN)
/SCL: R23.2, U10.2 (A), U_BQ1.26 (SCL/SPI_CLK), U_ESP1.30 (RXD0/IO20)
/SCL_BQ2: R27.2, U11.6 (SCL2), U_BQ2.26 (SCL/SPI_CLK)
/SCL_ISO1: R25.2, U10.4 (B), U11.3 (SCL1)
/SDA: R22.2, U9.2 (A), U_BQ1.27 (SDA/SPI_MISO), U_ESP1.31 (TXD0/IO21)
/SDA_BQ2: R26.2, U11.7 (SDA2), U_BQ2.27 (SDA/SPI_MISO)
/SDA_ISO1: R24.2, U9.4 (B), U11.2 (SDA1)
/SENSE_N: NT2.2, R111.1
/SENSE_P: NT1.2, R110.1
/SRN: C110.2, R111.2, U_BQ1.20 (SRN)
/SRP: C110.1, R110.2, U_BQ1.18 (SRP)
/SW: D2.1 (K), L1.1, U4.1 (SW)
/T1_EXT: J_T1.1, R112.1
/T2_EXT: J_T2.1, R113.1
/T3_EXT: J_T3.1, R114.1
/T4_EXT: J_T4.1, R115.1
/TAP0_F: C_F1.2, R_B33.2, U_BQ1.16 (VC0)
/TAP1_F: C_F1.1, C_F2.2, R_B32.2, U_BQ1.15 (VC1)
/TAP2_F: C_F2.1, C_F3.2, R_B31.2, U_BQ1.14 (VC2)
/TAP3_F: C_F3.1, C_F4.2, R_B30.2, U_BQ1.13 (VC3)
/TAP4_F: C_F4.1, C_F5.2, R_B29.2, U_BQ1.12 (VC4)
/TAP5_F: C_F5.1, C_F6.2, R_B28.2, U_BQ1.11 (VC5)
/TAP6_F: C_F6.1, C_F7.2, R_B27.2, U_BQ1.10 (VC6)
/TAP7_F: C_F7.1, C_F8.2, R_B26.2, U_BQ1.9 (VC7)
/TAP8_F: C_F8.1, C_F9.2, R_B25.2, U_BQ1.8 (VC8)
/TAP9_F: C_F9.1, C_F10.2, R_B24.2, U_BQ1.7 (VC9)
/TAP10_F: C_F10.1, C_F11.2, R_B23.2, U_BQ1.6 (VC10)
/TAP11_F: C_F11.1, C_F12.2, R_B22.2, U_BQ1.5 (VC11)
/TAP12_F: C_F12.1, C_F13.2, R_B21.2, U_BQ1.4 (VC12)
/TAP13_F: C_F13.1, C_F14.2, R_B20.2, U_BQ1.3 (VC13)
/TAP14_F: C_F14.1, C_F15.2, R_B19.2, U_BQ1.2 (VC14)
/TAP15_F: C_F15.1, C_F16.2, R_B18.2, U_BQ1.1 (VC15)
/TAP16_F: C_F16.1, C_F17.2, R_B17.2, U_BQ1.48 (VC16), U_BQ2.16 (VC0)
/TAP17_F: C_F17.1, C_F18.2, R_B16.2, U_BQ2.15 (VC1)
/TAP18_F: C_F18.1, C_F19.2, R_B15.2, U_BQ2.14 (VC2)
/TAP19_F: C_F19.1, C_F20.2, R_B14.2, U_BQ2.13 (VC3)
/TAP20_F: C_F20.1, C_F21.2, R_B13.2, U_BQ2.12 (VC4)
/TAP21_F: C_F21.1, C_F22.2, R_B12.2, U_BQ2.11 (VC5)
/TAP22_F: C_F22.1, C_F23.2, R_B11.2, U_BQ2.10 (VC6)
/TAP23_F: C_F23.1, C_F24.2, R_B10.2, U_BQ2.9 (VC7)
/TAP24_F: C_F24.1, C_F25.2, R_B9.2, U_BQ2.8 (VC8)
/TAP25_F: C_F25.1, C_F26.2, R_B8.2, U_BQ2.7 (VC9)
/TAP26_F: C_F26.1, C_F27.2, R_B7.2, U_BQ2.6 (VC10)
/TAP27_F: C_F27.1, C_F28.2, R_B6.2, U_BQ2.5 (VC11)
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
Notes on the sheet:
Cell taps: plugs, R_B1-R_B33 input resistors, filter capacitors
Lower monitor U_BQ1 (cells 1-16, reference GND) + current sense + temperatures
Upper monitor U_BQ2 (cells 17-32, reference CELL16)
Charge path: back-to-back FETs, photovoltaic gate drive, shunt, dividers
Power: 140 V buck to 5 V, USB OR-ing, 3.3 V LDO
ESP32-C3 (VBMS32 firmware pins), USB, wake button, buzzer
Upper-monitor I2C link (bus switch + ISO1640 + switched supply) and isolated CAN
Power flags (nets fed only by passive parts or connectors)
